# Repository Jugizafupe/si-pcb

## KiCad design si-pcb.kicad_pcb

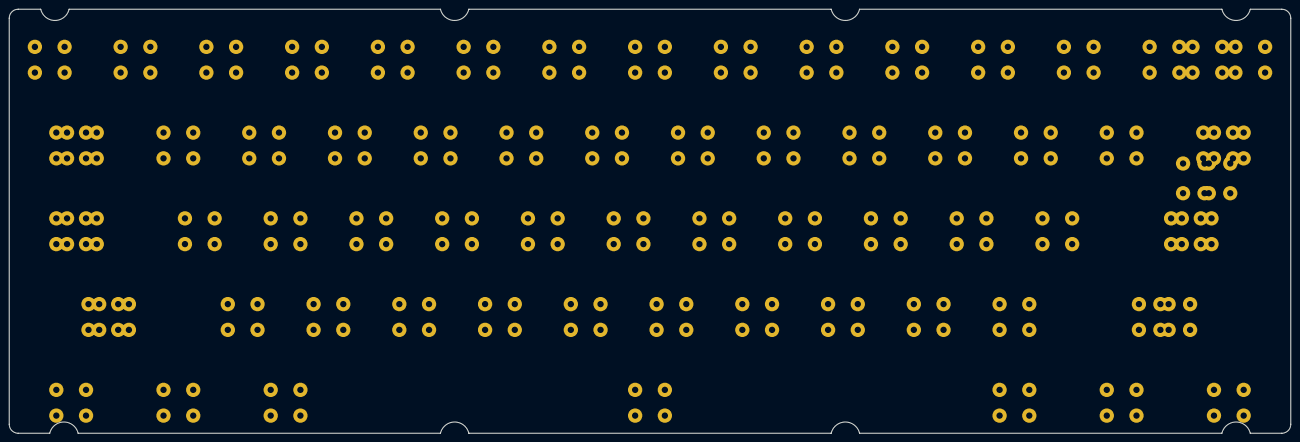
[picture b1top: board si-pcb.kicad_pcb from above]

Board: 2 copper layers, 284.7 x 94.2 mm, 70 parts (0 on the bottom side), 22 nets, no tracks yet.

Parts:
MX0, MX1, MX2, MX3, MX4, MX5, MX6, MX7, MX8, MX9, MX10, MX11, MX12, MX13, MX14-0, MX16, MX17, MX18, MX19, MX20, MX21, MX22, MX23, MX24, MX25, MX26, MX27, MX30, MX31, MX32, MX33, MX34, MX35, MX36, MX37, MX38, MX39, MX40, MX45, MX46, MX47, MX48, MX49, MX50, MX51, MX52, MX53, MX54, MX57, MX61: MX-NoLED; Hitek725-1U
MX14-1, MX55-1: MX-NoLED; Hitek725-1U-reversed
MX15-0, MX28-0, MX29-1, MX56, MX58, MX60, MX62: MX-NoLED; Hitek725-1.5U
MX15-1, MX28-1: MX-NoLED; Hitek725-1.25U
MX29-0: MX-NoLED; Hitek725-1.75U
MX42-0, MX43-0: MX-NoLED; Hitek725-2.25U
MX42-1, MX43-1: MX-NoLED; Hitek725-2U
MX42-3: MX-NoLED-SI; Hitek725-BigAssEnter-separated-pins
MX42-4: MX-NoLED-SI; Hitek725-BigAssEnter-reversed
MX55-0: MX-NoLED; Hitek725-2.75U
MX59: MX-NoLED; Hitek725-7U

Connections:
Col0: MX0.1 (COL), MX15-0.1 (COL), MX15-1.1 (COL), MX29-0.1 (COL), MX29-1.1 (COL), MX43-0.1 (COL), MX43-1.1 (COL), MX56.1 (COL)
Col1: MX1.1 (COL), MX16.1 (COL), MX30.1 (COL), MX57.1 (COL)
Col2: MX2.1 (COL), MX17.1 (COL), MX31.1 (COL), MX45.1 (COL), MX58.1 (COL)
Col3: MX3.1 (COL), MX18.1 (COL), MX32.1 (COL), MX46.1 (COL)
Col4: MX4.1 (COL), MX19.1 (COL), MX33.1 (COL), MX47.1 (COL)
Col5: MX5.1 (COL), MX20.1 (COL), MX34.1 (COL), MX48.1 (COL)
Col6: MX6.1 (COL), MX21.1 (COL), MX35.1 (COL), MX49.1 (COL), MX59.1 (COL)
Col7: MX7.1 (COL), MX22.1 (COL), MX36.1 (COL), MX50.1 (COL)
Col8: MX8.1 (COL), MX23.1 (COL), MX37.1 (COL), MX51.1 (COL)
Col9: MX9.1 (COL), MX24.1 (COL), MX38.1 (COL), MX52.1 (COL)
Col10: MX10.1 (COL), MX25.1 (COL), MX39.1 (COL), MX53.1 (COL)
Col11: MX11.1 (COL), MX26.1 (COL), MX40.1 (COL), MX54.1 (COL), MX60.1 (COL)
Col12: MX12.1 (COL), MX27.1 (COL), MX55-0.1 (COL), MX55-1.1 (COL), MX61.1 (COL)
Col13: MX13.1 (COL), MX28-0.1 (COL), MX28-1.1 (COL), MX42-0.1 (COL), MX42-1.1 (COL), MX42-3.1 (COL), MX42-4.1 (COL), MX62.1 (COL)
Col14: MX14-0.1 (COL), MX14-1.1 (COL)
unnamed: MX14-0.2 (ROW), MX14-1.2 (ROW)
unnamed: MX15-0.2 (ROW), MX15-1.2 (ROW)
unnamed: MX28-0.2 (ROW), MX28-1.2 (ROW)
unnamed: MX29-0.2 (ROW), MX29-1.2 (ROW)
unnamed: MX42-0.2 (ROW), MX42-1.2 (ROW), MX42-3.2 (ROW), MX42-4.2 (ROW)
unnamed: MX43-0.2 (ROW), MX43-1.2 (ROW)
unnamed: MX55-0.2 (ROW), MX55-1.2 (ROW)

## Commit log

2021-02-23 Import libraries
2021-02-23 Create switches positions
2021-02-23 Add meta files
2021-02-24 Edit BEA switch symbols
2021-02-25 Add via layout json in meta
